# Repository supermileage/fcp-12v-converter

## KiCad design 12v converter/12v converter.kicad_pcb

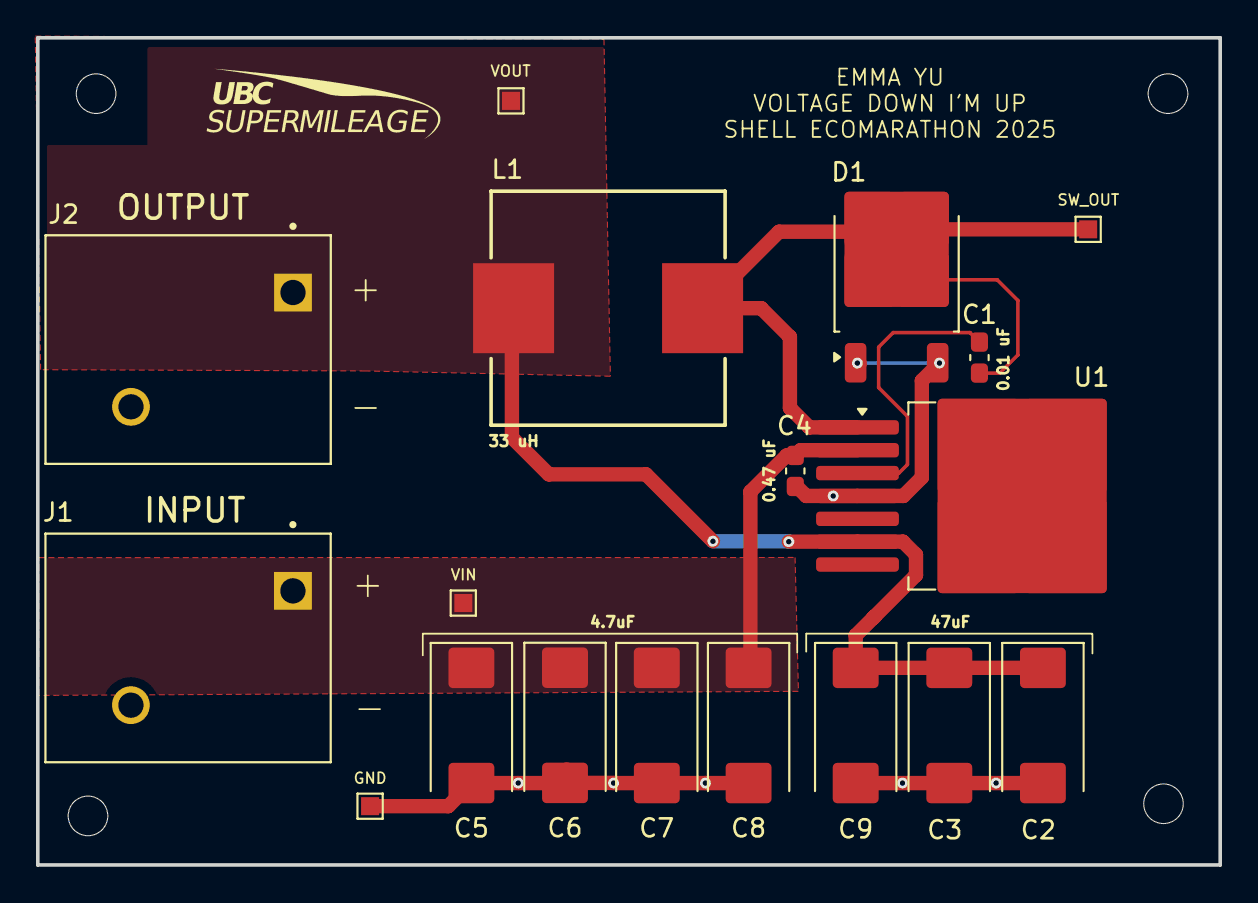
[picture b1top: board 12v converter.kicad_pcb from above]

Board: 2 copper layers, 65.7 x 46.0 mm, 22 parts (0 on the bottom side), 5 nets.

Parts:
C1: 0.01 uF; C_0603_1608Metric_Pad1.08x0.95mm_HandSolder
C2, C3, C9: 47 uF; CP_EIA-7343-43_Kemet-X_Pad2.25x2.55mm_HandSolder
C4: 0.47 uF; C_0603_1608Metric_Pad1.08x0.95mm_HandSolder
C5, C6, C7, C8: 4.7 uF; CP_EIA-7343-31_Kemet-D_Pad2.25x2.55mm_HandSolder
D1: D_Schottky_Filled; TO-252-2
GND: GND; TestPoint_Pad_1.0x1.0mm
H1, H2, H3, H4: MountingHole; MountingHole_2.2mm_M2
J1, J2: Conn_01x02_Socket; PHOENIX_1777545
L1: 33 uH; WE-HCI_1365
SW_OUT: switch_output; TestPoint_Pad_1.0x1.0mm
U1: LM2674N-3.3; TO-263-7_TabPin8
VIN: VIN; TestPoint_Pad_1.0x1.0mm
VOUT: VOUT; TestPoint_Pad_1.0x1.0mm

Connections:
/SW_OUT: C1.2, D1.1 (K), L1.2, SW_OUT.1, U1.1 (VSW)
/VOUT: C2.1, C3.1, C9.1, J2.1, L1.1, U1.6 (FB), VOUT.1
GND: C2.2, C3.2, C4.2, C5.2, C6.2, C7.2, C8.2, C9.2, D1.2 (A), GND.1, J1.2, J2.2, U1.4 (GND)
unnamed: C1.1, U1.3 (CB)
VIN: C4.1, C5.1, C6.1, C7.1, C8.1, J1.1, U1.2 (VIN), VIN.1

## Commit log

2024-11-17 created initial kicad project files
2024-12-09 created schematic for 12v converter
2025-01-05 Added power flags, added J1 and J2 symbols for input and output, put no connect symbol on ON/OFF, created SW_OUT labels, fixed annotation error
2025-01-11 nothing really changed
2025-01-11 nothing
2025-01-11 configured custom footprint folder path as project specific library
2025-01-13 started PCB, updated footprints for inductor and J1 and J2 in schematic
2025-01-14 Completed layout. Fixed incorrect schematic connections. Converted supermileage logo to silkscreen and added to layout
2025-01-14 silkscreen labels for i/o and vias for diode
2025-01-14 test points, labels
2025-01-14 rearrangmenet, silkscreen stuff
2025-01-14 Fixed silkscreen RefDes labels, made component values visible, added mounting holes with keepout zones around them. Generated gerber, drill and drill map files
2025-01-18 generated .STEP file of board outline (holes included)
2025-01-18 generated new .STEP file, added mesurements to PCB layout view
2025-02-03 pin reassignment, rerouting and changing position of SW_OUT and GND test points
2025-02-04 changed D1 footprint from TO-252-3 to TO-252 then altered it (only on board) to make the outer pins GND and the pad SW_OUT
2025-02-04 generated gerber and drill files
